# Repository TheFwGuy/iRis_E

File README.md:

iRis project with Energia

To compile, Set Energia to have the library included and open iRis.ino.
This directory should be placed in the main directory where the sketches are
kept.

It is necessary to have these libraries installed in the library directory:

- LCD_protocol_terminal
- LCD_screen
- LiquidCrystal
- SD
- Adafruit_Sensor_master
- Adafruit_TSL2561_master

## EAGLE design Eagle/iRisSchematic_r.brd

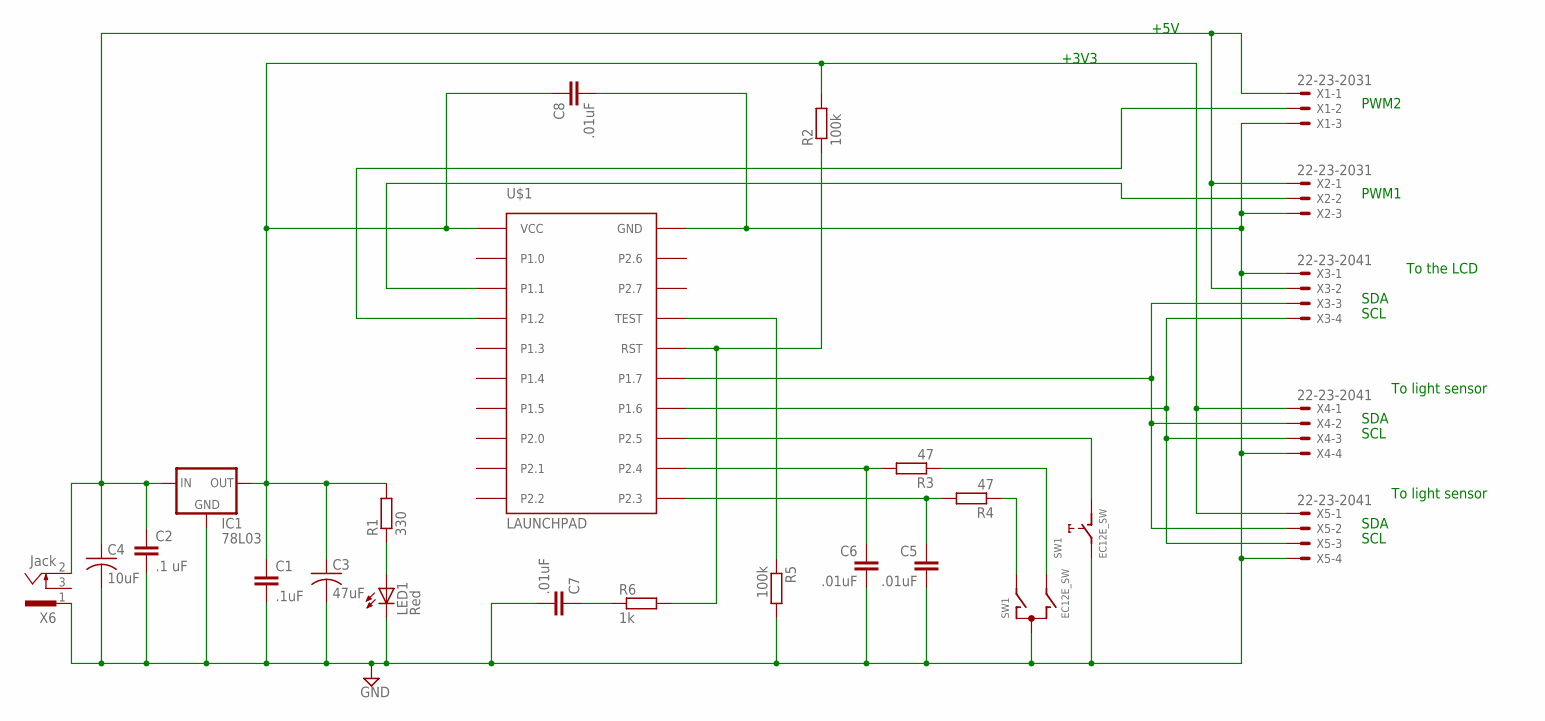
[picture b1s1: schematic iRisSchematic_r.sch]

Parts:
C1: .1uF; C2.5-2
C2: .1 uF; C2.5-2
C3: 47uF; C025-030X050
C4: 10uF; C025-030X050
C5, C6, C7, C8: .01uF; C2.5-2
IC1: 78L03; 78LXX
LED1: Red; LED_LD260
R1: 330; 0204/5
R2, R5: 100k; 0204/5
R3, R4: 47; 0204/5
R6: 1k; 0204/5
SW1: EC12E_SW; ALPS_EC12E_SW
U$1: LAUNCHPAD
X1, X2: 22-23-2031
X3, X4, X5: 22-23-2041
X6: Jack; SCD-014-A

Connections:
GND: C1.2, C2.2, C3.2, C4.2, C5.2, C6.2, C7.2, C8.2, IC1.GND, LED1.K (C), R5.2, SW1.C, SW1.E (2), U$1.GND, X1.3, X2.3, X3.1, X4.4, X5.4, X6.1
unnamed: LED1.A, R1.1
unnamed: SW1.D (1), U$1.P2.5
unnamed: C5.1, R4.2, U$1.P2.3
unnamed: C6.1, R3.2, U$1.P2.4
unnamed: U$1.P1.1, X2.2
unnamed: R5.1, U$1.TEST
unnamed: U$1.P1.6, X3.4, X4.3, X5.3
unnamed: R2.1, R6.2, U$1.RST
unnamed: C1.1, C3.1, C8.1, IC1.OUT, R1.2, R2.2, U$1.VCC, X4.1, X5.1
unnamed: R3.1, SW1.B
unnamed: R4.1, SW1.A
unnamed: C7.1, R6.1
unnamed: C2.1, C4.1, IC1.IN, X1.1, X2.1, X3.2, X6.2
unnamed: U$1.P1.2, X1.2
unnamed: U$1.P1.7, X3.3, X4.2, X5.2

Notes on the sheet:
PWM2
PWM1
SCL
SDA
+3V3
+5V
To light sensor
To the LCD

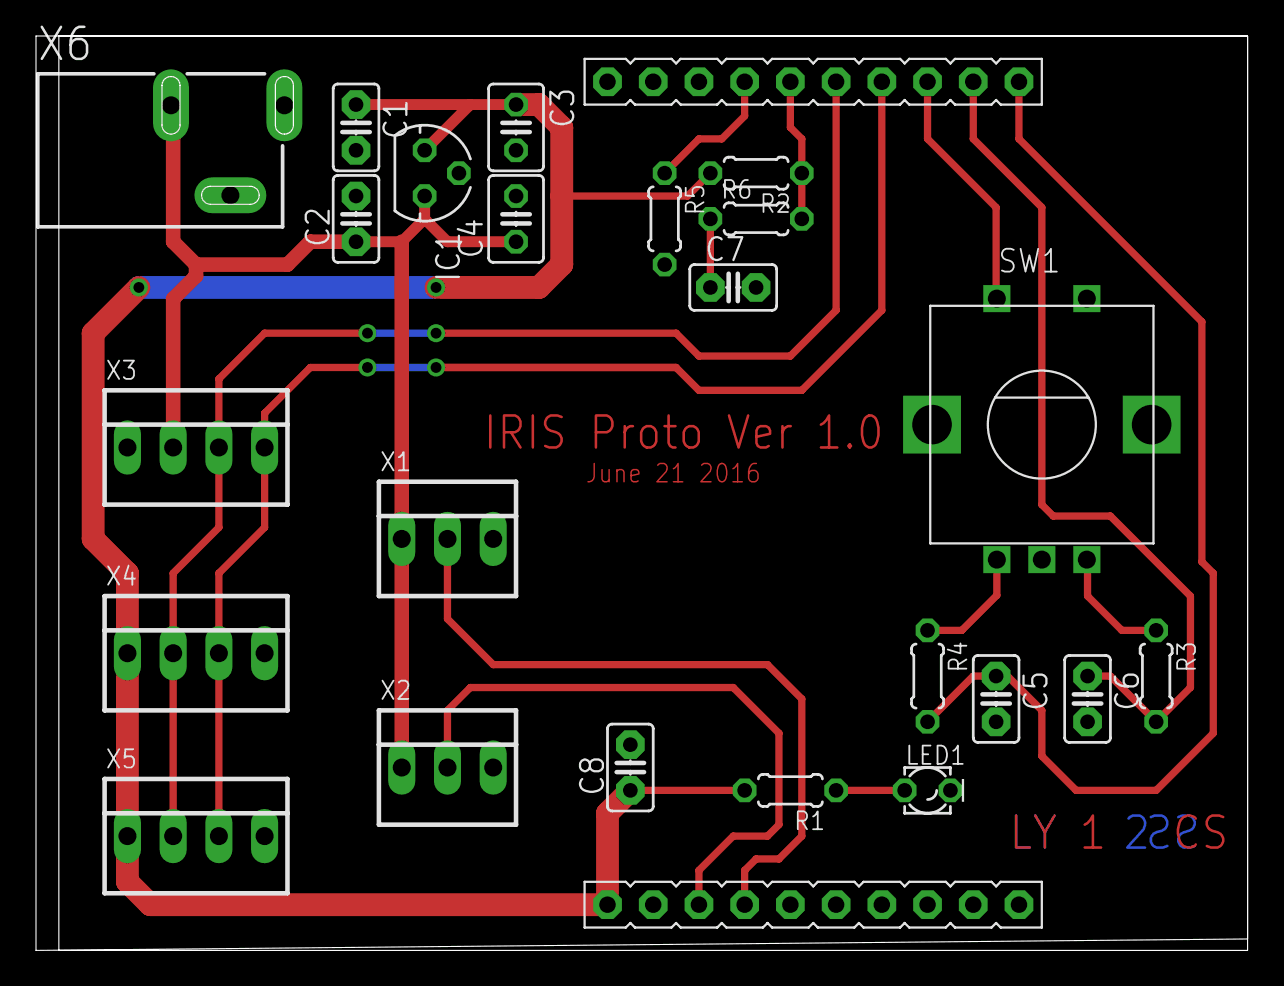
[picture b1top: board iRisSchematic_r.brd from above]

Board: 2 copper layers, 67.3 x 50.8 mm, 24 parts (0 on the bottom side), 16 nets.

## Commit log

2015-11-21 Derived from UVBoxTimer - basic handling PWM and encoder
2015-11-21 Added TSL2561 management and light control iris
2015-12-22 Added second sensor reading - calibration - menu selection
2017-09-18 Moved in Fidocad dir
2017-09-18 Added Eagle schematics prototype on Launchpad
2017-09-18 Moved from generic schematic - old
